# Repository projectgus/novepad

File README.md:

Development of an adapter board design for [Kosagi Novena](http://kosagi.com/w/index.php?title=Novena_Main_Page) LVDS interface to connect to the "iPad 3" QXGA 2048x1536 eDP LCD panel (aka LG LP097QX1-SPC1 and related models). Possibly also a touch screen interface to suit that display...

* [Schematic PDF here](https://github.com/projectgus/novepad/raw/master/novepad-schematic.pdf)
* [Kosagi forum thread here](http://www.kosagi.com/forums/viewtopic.php?id=58).

**INITIAL PROTOTYPE STAGE, NOT A THING YET**

Very closely modelled on Bunnie's existing Novena eDP adapter, with additions. LVDS connection cable from Novena should be the same on both boards.

Designed using KiCad (2014-07-25, any recent version should be OK to open the files). [Gerbers are available from the releases page](https://github.com/projectgus/novepad/releases/).

# Additions to the Novena eDP design

* Backlight driver (2x TI [TPS61181](http://www.ti.com/product/tps61181))
* Touch screen controller Focaltech [FT5816LPC](http://www.focaltech-systems.com/En/solutions.aspx?CateID=54) with i2c and USB interfaces. There's a strong chance this will never work (lack of public documentation on controller or digitizer).
* 4 eDP lanes out of IT6251 eDP converter instead of the 2 used on Novena eDP board.

# Notes

* Has a lot of numbered test points and 0R resistors due to undocumented or unknown factors.
* Has cut trace jumpers for some key power connections, can be cut to measure power consumption.

# Board Stackup

4 layer board, 1oz copper (35um). Desired stackup is:

* Front copper
* 0.2mm prepreg
* GND (Inner1)
* 1.2mm prepreg
* VCC (Inner2)
* 0.2mm prepreg
* Back

(This matches standard 4 layer stackup for my usual prototype PCB supplier, [Hackvana](http://hackvana.com)).)

The 100 ohm differential microstrip traces (LVDS, eDP) are routed as 0.2mm trace / 0.15mm spacing (~8/6 imperial), at least where possible. This yields estimates in the range of 99.5-102ohm differential impedance depending on who you ask (assuming Er 4.4, calculated using [TNT Field Solver](http://mmtl.sourceforge.net/) and [Jean Nicolle's impedance calculator](http://www.fedevel.com/welldoneblog/2011/08/pcb-impedance-calculator-single-ended-differential-pair/).

# Resources

## Novena designs

Yay OSHW!

* http://kosagi.com/w/index.php?title=Novena_PVT_Design_Source

## iPad display/connectors

* http://emerythacks.blogspot.com.au/2013/04/connecting-ipad-retina-lcd-to-pc.html
* http://mikesmods.com/mm-wp/?s=ipad+3

## Photos of IT6251

You know a chip is going to be fun when **photos** of PCBs that use it become a useful resource to complement the datasheet.

* [overclock.net post with high-res photo of top of board](http://www.overclock.net/t/1225919/yamakasi-catleap-monitor-club/2110#post_16887300)
* [overclock.net lower-res photos incl back of board (no components)](http://www.overclock.net/t/1304102/catleap-q270-replacement-board#post_18163044)

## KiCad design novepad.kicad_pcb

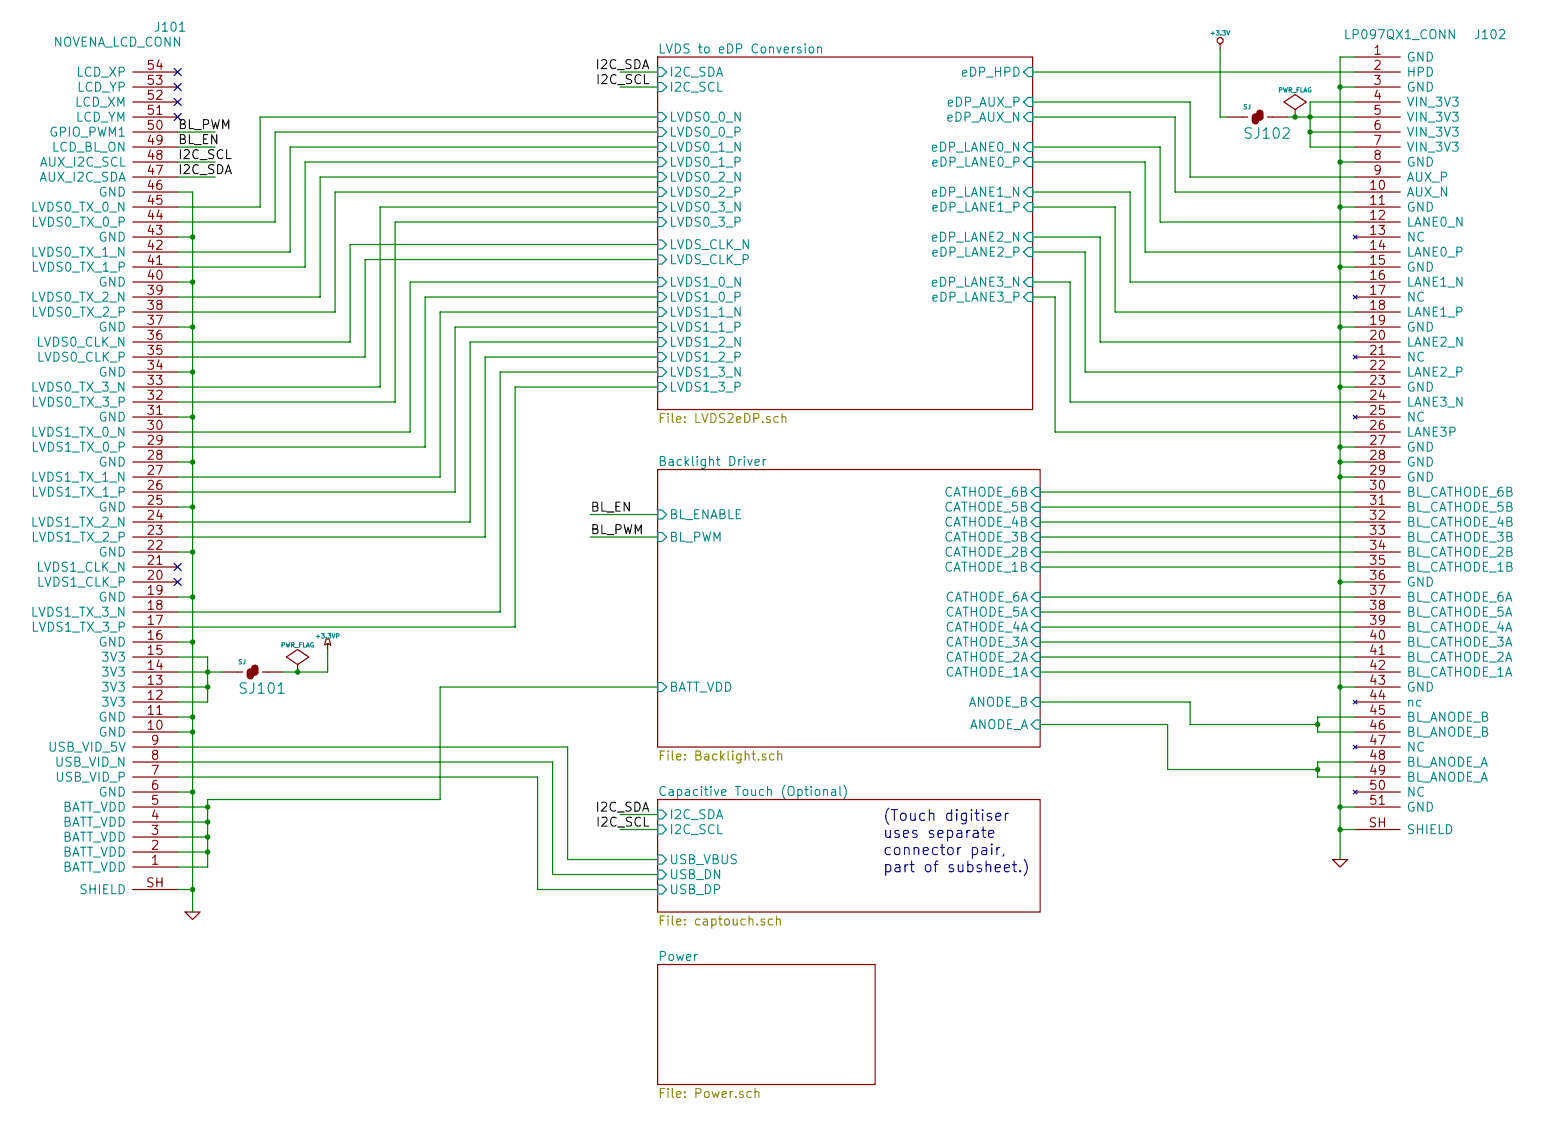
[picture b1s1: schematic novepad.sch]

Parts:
J101: NOVENA_LCD_CONN; MOLEX_51926_5494
J102: LP097QX1_CONN; MOLEX_502250_8051
SJ101, SJ102: SJ; SJ_SHORTED

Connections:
+3.3V: SJ102.1; also elsewhere on the board
+3.3VP: SJ101.2; also elsewhere on the board
/Backlight Driver/ANODE_A: J102.48 (BL_ANODE_A), J102.49 (BL_ANODE_A); also elsewhere on the board
/Backlight Driver/ANODE_B: J102.45 (BL_ANODE_B), J102.46 (BL_ANODE_B); also elsewhere on the board
/Backlight Driver/BATT_VDD: J101.1 (BATT_VDD), J101.2 (BATT_VDD), J101.3 (BATT_VDD), J101.4 (BATT_VDD), J101.5 (BATT_VDD); also elsewhere on the board
/Backlight Driver/BL_ENABLE: J101.49 (LCD_BL_ON); also elsewhere on the board
/Backlight Driver/BL_PWM: J101.50 (GPIO_PWM1); also elsewhere on the board
/Backlight Driver/CATHODE_1A: J102.42 (BL_CATHODE_1A); also elsewhere on the board
/Backlight Driver/CATHODE_1B: J102.35 (BL_CATHODE_1B); also elsewhere on the board
/Backlight Driver/CATHODE_2A: J102.41 (BL_CATHODE_2A); also elsewhere on the board
/Backlight Driver/CATHODE_2B: J102.34 (BL_CATHODE_2B); also elsewhere on the board
/Backlight Driver/CATHODE_3A: J102.40 (BL_CATHODE_3A); also elsewhere on the board
/Backlight Driver/CATHODE_3B: J102.33 (BL_CATHODE_3B); also elsewhere on the board
/Backlight Driver/CATHODE_4A: J102.39 (BL_CATHODE_4A); also elsewhere on the board
/Backlight Driver/CATHODE_4B: J102.32 (BL_CATHODE_4B); also elsewhere on the board
/Backlight Driver/CATHODE_5A: J102.38 (BL_CATHODE_5A); also elsewhere on the board
/Backlight Driver/CATHODE_5B: J102.31 (BL_CATHODE_5B); also elsewhere on the board
/Backlight Driver/CATHODE_6A: J102.37 (BL_CATHODE_6A); also elsewhere on the board
/Backlight Driver/CATHODE_6B: J102.30 (BL_CATHODE_6B); also elsewhere on the board
/Capacitive Touch (Optional)/I2C_SCL: J101.48 (AUX_I2C_SCL); also elsewhere on the board
/Capacitive Touch (Optional)/I2C_SDA: J101.47 (AUX_I2C_SDA); also elsewhere on the board
/Capacitive Touch (Optional)/USB_DN: J101.8 (USB_VID_N); also elsewhere on the board
/Capacitive Touch (Optional)/USB_DP: J101.7 (USB_VID_P); also elsewhere on the board
/Capacitive Touch (Optional)/USB_VBUS: J101.9 (USB_VID_5V); also elsewhere on the board
/LVDS to eDP Conversion/LVDS0_0_N: J101.45 (LVDS0_TX_0_N); also elsewhere on the board
/LVDS to eDP Conversion/LVDS0_0_P: J101.44 (LVDS0_TX_0_P); also elsewhere on the board
/LVDS to eDP Conversion/LVDS0_1_N: J101.42 (LVDS0_TX_1_N); also elsewhere on the board
/LVDS to eDP Conversion/LVDS0_1_P: J101.41 (LVDS0_TX_1_P); also elsewhere on the board
/LVDS to eDP Conversion/LVDS0_2_N: J101.39 (LVDS0_TX_2_N); also elsewhere on the board
/LVDS to eDP Conversion/LVDS0_2_P: J101.38 (LVDS0_TX_2_P); also elsewhere on the board
/LVDS to eDP Conversion/LVDS0_3_N: J101.33 (LVDS0_TX_3_N); also elsewhere on the board
/LVDS to eDP Conversion/LVDS0_3_P: J101.32 (LVDS0_TX_3_P); also elsewhere on the board
/LVDS to eDP Conversion/LVDS1_0_N: J101.30 (LVDS1_TX_0_N); also elsewhere on the board
/LVDS to eDP Conversion/LVDS1_0_P: J101.29 (LVDS1_TX_0_P); also elsewhere on the board
/LVDS to eDP Conversion/LVDS1_1_N: J101.27 (LVDS1_TX_1_N); also elsewhere on the board
/LVDS to eDP Conversion/LVDS1_1_P: J101.26 (LVDS1_TX_1_P); also elsewhere on the board
/LVDS to eDP Conversion/LVDS1_2_N: J101.24 (LVDS1_TX_2_N); also elsewhere on the board
/LVDS to eDP Conversion/LVDS1_2_P: J101.23 (LVDS1_TX_2_P); also elsewhere on the board
/LVDS to eDP Conversion/LVDS1_3_N: J101.18 (LVDS1_TX_3_N); also elsewhere on the board
/LVDS to eDP Conversion/LVDS1_3_P: J101.17 (LVDS1_TX_3_P); also elsewhere on the board
/LVDS to eDP Conversion/LVDS_CLK_N: J101.36 (LVDS0_CLK_N); also elsewhere on the board
/LVDS to eDP Conversion/LVDS_CLK_P: J101.35 (LVDS0_CLK_P); also elsewhere on the board
/LVDS to eDP Conversion/eDP_AUX_N: J102.10 (AUX_N); also elsewhere on the board
/LVDS to eDP Conversion/eDP_AUX_P: J102.9 (AUX_P); also elsewhere on the board
/LVDS to eDP Conversion/eDP_HPD: J102.2 (HPD); also elsewhere on the board
/LVDS to eDP Conversion/eDP_LANE0_N: J102.12 (LANE0_N); also elsewhere on the board
/LVDS to eDP Conversion/eDP_LANE0_P: J102.14 (LANE0_P); also elsewhere on the board
/LVDS to eDP Conversion/eDP_LANE1_N: J102.16 (LANE1_N); also elsewhere on the board
/LVDS to eDP Conversion/eDP_LANE1_P: J102.18 (LANE1_P); also elsewhere on the board
/LVDS to eDP Conversion/eDP_LANE2_N: J102.20 (LANE2_N); also elsewhere on the board
/LVDS to eDP Conversion/eDP_LANE2_P: J102.22 (LANE2_P); also elsewhere on the board
/LVDS to eDP Conversion/eDP_LANE3_N: J102.24 (LANE3_N); also elsewhere on the board
/LVDS to eDP Conversion/eDP_LANE3_P: J102.26 (LANE3P); also elsewhere on the board
GND: J101.6 (GND), J101.10 (GND), J101.11 (GND), J101.16 (GND), J101.19 (GND), J101.22 (GND), J101.25 (GND), J101.28 (GND), J101.31 (GND), J101.34 (GND), J101.37 (GND), J101.40 (GND), J101.43 (GND), J101.46 (GND), J101.SH (SHIELD), J102.1 (GND), J102.3 (GND), J102.8 (GND), J102.11 (GND), J102.15 (GND), J102.19 (GND), J102.23 (GND), J102.27 (GND), J102.28 (GND), J102.29 (GND), J102.36 (GND), J102.43 (GND), J102.51 (GND), J102.SH (SHIELD); also elsewhere on the board
unnamed: J101.12 (3V3), J101.13 (3V3), J101.14 (3V3), J101.15 (3V3), SJ101.1
unnamed: J102.4 (VIN_3V3), J102.5 (VIN_3V3), J102.6 (VIN_3V3), J102.7 (VIN_3V3), SJ102.2

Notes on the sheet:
(Touch digitiser uses separate connector pair, part of subsheet.)

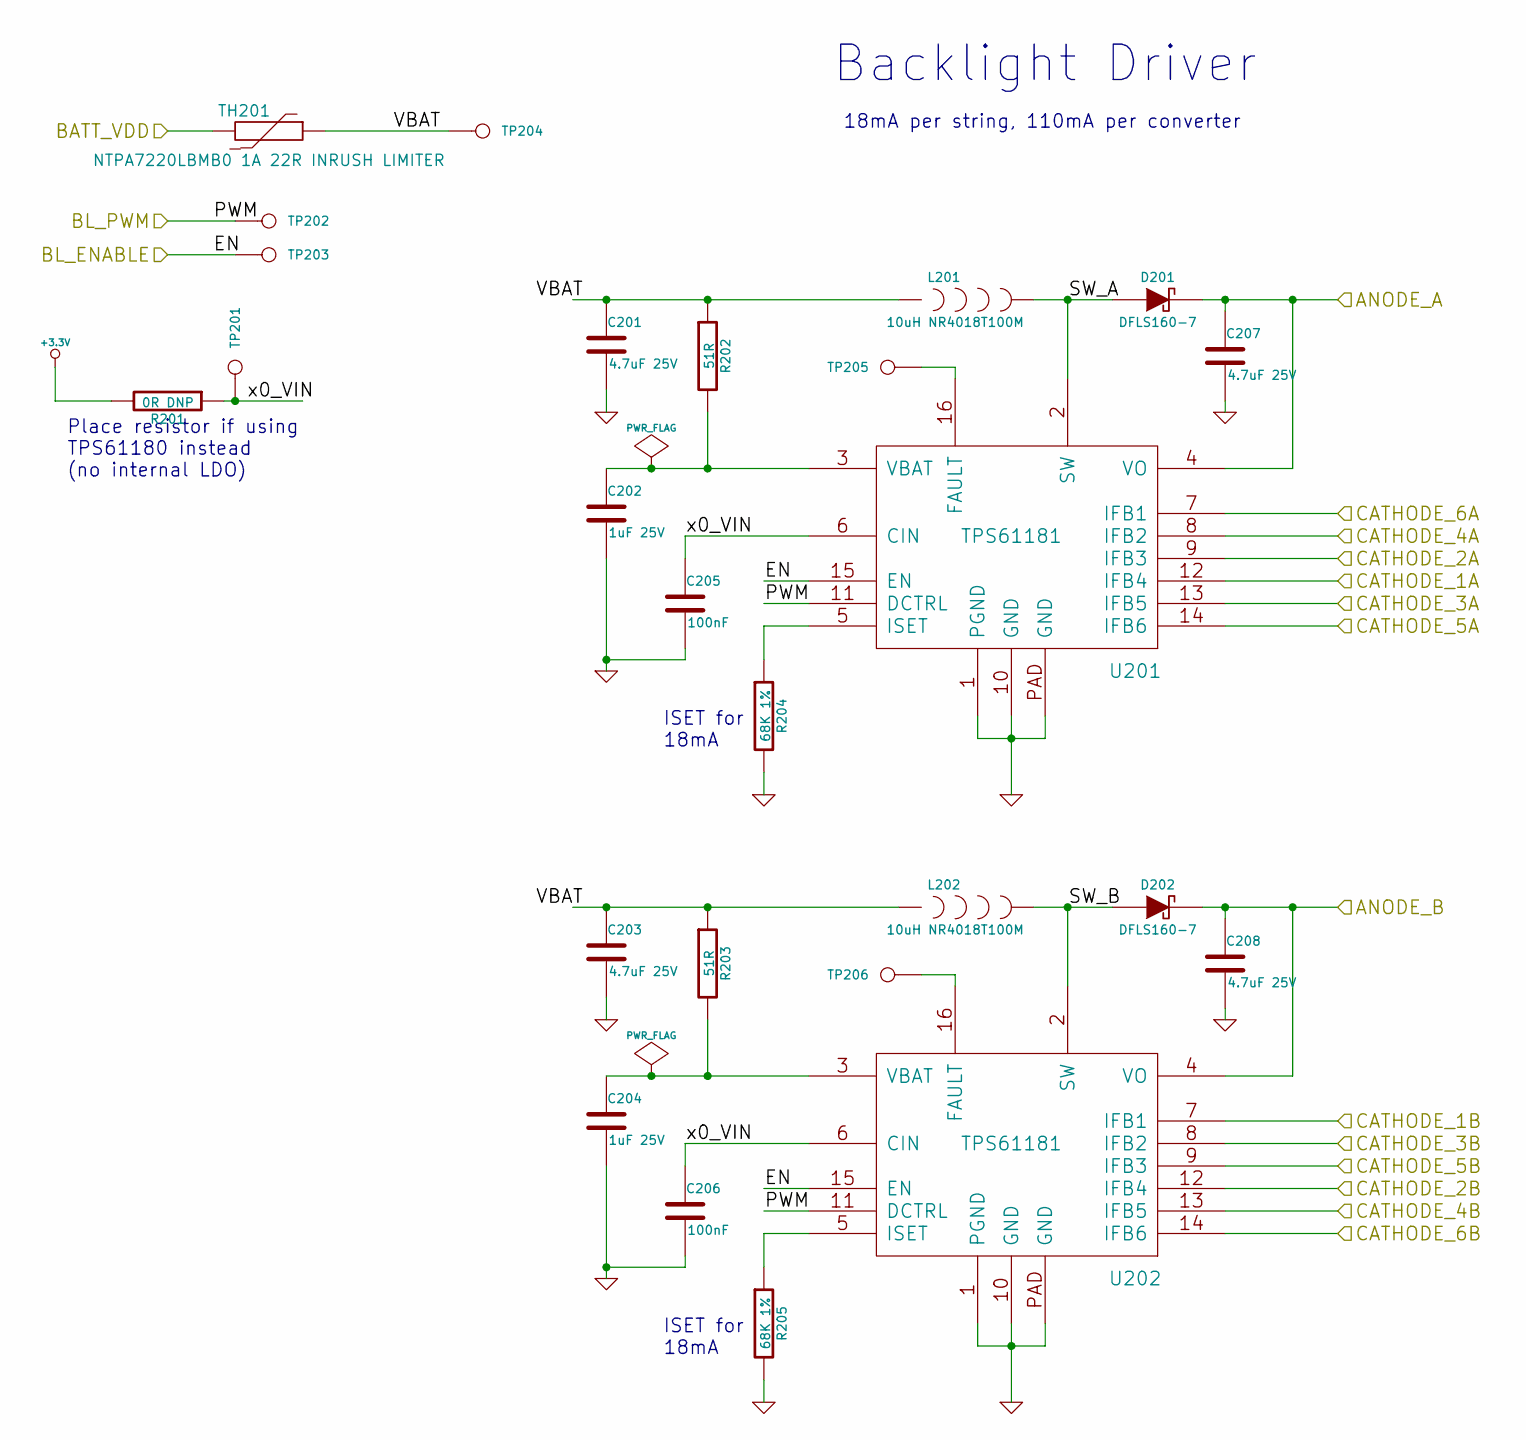
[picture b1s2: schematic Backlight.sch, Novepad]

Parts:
C201, C203, C207, C208: 4.7uF 25V; 0805
C202, C204: 1uF 25V; 0603
C205, C206: 100nF; C0402
D201, D202: DFLS160-7; POWERDI123_DIODE
L201, L202: 10uH NR4018T100M; NR4018_IND
R201: 0R DNP; 0603
R202, R203: 51R; 0603
R204, R205: 68K 1%; 0603
TH201: NTPA7220LBMB0 1A 22R INRUSH LIMITER; PTH_2HOLE_5MM
TP201, TP202, TP203, TP204, TP205, TP206: CONN_1; SMD_TEST_POINT
U201, U202: TPS61181; QFN50P300X300X80-17N

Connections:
+3.3V: R201.2; also elsewhere on the board
/Backlight Driver/ANODE_A: C207.1, D201.K, U201.4 (VO); also elsewhere on the board
/Backlight Driver/ANODE_B: C208.1, D202.K, U202.4 (VO); also elsewhere on the board
/Backlight Driver/BATT_VDD: TH201.2; also elsewhere on the board
/Backlight Driver/BL_ENABLE: TP203.1, U201.15 (EN), U202.15 (EN); also elsewhere on the board
/Backlight Driver/BL_PWM: TP202.1, U201.11 (DCTRL), U202.11 (DCTRL); also elsewhere on the board
/Backlight Driver/CATHODE_1A: U201.12 (IFB4); also elsewhere on the board
/Backlight Driver/CATHODE_1B: U202.7 (IFB1); also elsewhere on the board
/Backlight Driver/CATHODE_2A: U201.9 (IFB3); also elsewhere on the board
/Backlight Driver/CATHODE_2B: U202.12 (IFB4); also elsewhere on the board
/Backlight Driver/CATHODE_3A: U201.13 (IFB5); also elsewhere on the board
/Backlight Driver/CATHODE_3B: U202.8 (IFB2); also elsewhere on the board
/Backlight Driver/CATHODE_4A: U201.8 (IFB2); also elsewhere on the board
/Backlight Driver/CATHODE_4B: U202.13 (IFB5); also elsewhere on the board
/Backlight Driver/CATHODE_5A: U201.14 (IFB6); also elsewhere on the board
/Backlight Driver/CATHODE_5B: U202.9 (IFB3); also elsewhere on the board
/Backlight Driver/CATHODE_6A: U201.7 (IFB1); also elsewhere on the board
/Backlight Driver/CATHODE_6B: U202.14 (IFB6); also elsewhere on the board
/Backlight Driver/SW_A: D201.A, L201.2, U201.2 (SW)
/Backlight Driver/SW_B: D202.A, L202.2, U202.2 (SW)
/Backlight Driver/VBAT: C201.1, C203.1, L201.1, L202.1, R202.1, R203.1, TH201.1, TP204.1
/Backlight Driver/x0_VIN: C205.1, C206.1, R201.1, TP201.1, U201.6 (CIN), U202.6 (CIN)
GND: C201.2, C202.2, C203.2, C204.2, C205.2, C206.2, C207.2, C208.2, R204.2, R205.2, U201.1 (PGND), U201.10 (GND), U201.PAD (GND), U202.1 (PGND), U202.10 (GND), U202.PAD (GND); also elsewhere on the board
unnamed: C202.1, R202.2, U201.3 (VBAT)
unnamed: C204.1, R203.2, U202.3 (VBAT)
unnamed: R204.1, U201.5 (ISET)
unnamed: R205.1, U202.5 (ISET)
unnamed: TP205.1, U201.16 (FAULT)
unnamed: TP206.1, U202.16 (FAULT)

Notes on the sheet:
Place resistor if using TPS61180 instead (no internal LDO)
18mA per string, 110mA per converter
ISET for 18mA
Backlight Driver

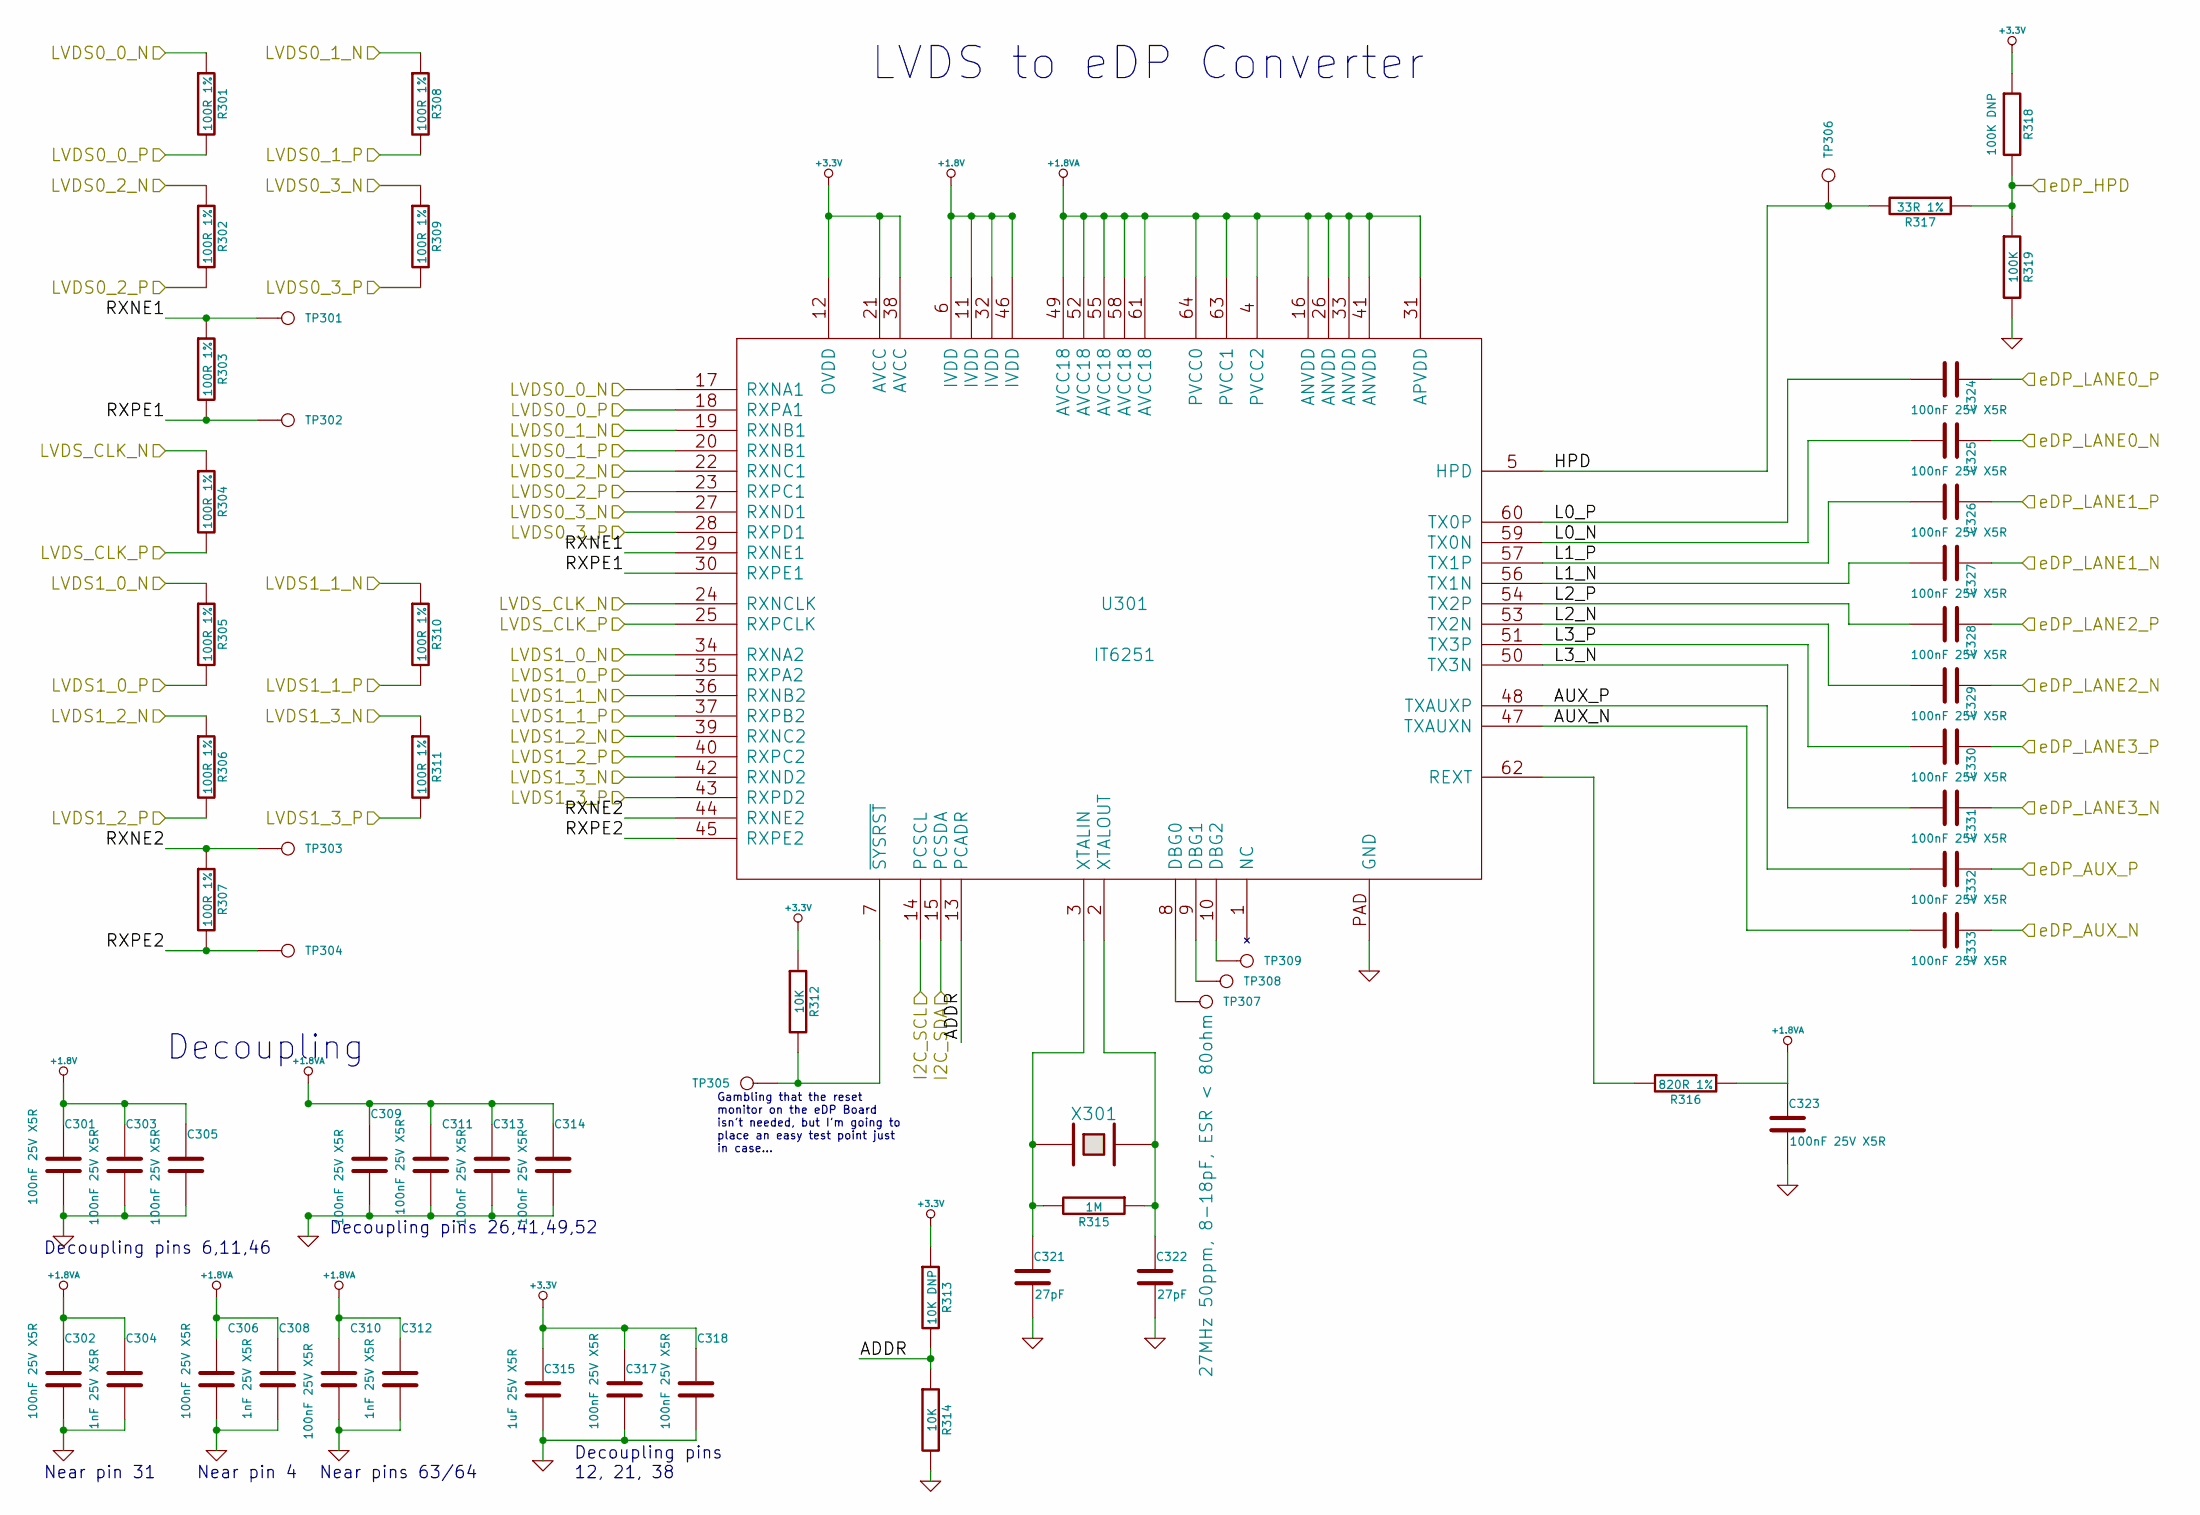
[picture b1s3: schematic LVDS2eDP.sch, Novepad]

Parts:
C301, C302, C303, C305, C306, C309, C310, C311, C313, C314, C317, C318, C323, C324, C325, C326, C327, C328, C329, C330, C331, C332, C333: 100nF 25V X5R; SMD-0402_c
C304, C308, C312: 1nF 25V X5R; SMD-0402_c
C315: 1uF 25V X5R; SMD-0402_c
C321, C322: 27pF; 0603
R301, R302, R303, R304, R305, R306, R307, R308, R309, R310, R311: 100R 1%; SMD-0402_r
R312, R314: 10K; 0603
R313: 10K DNP; 0603
R315: 1M; 0603
R316: 820R 1%; 0603
R317: 33R 1%; 0603
R318: 100K DNP; 0603
R319: 100K; 0603
TP301, TP302, TP303, TP304, TP305, TP306, TP307, TP308, TP309: CONN_1; SMD_TEST_POINT
U301: IT6251; QFN50P900X900X100-65N
X301: 27MHz 50ppm, 8-18pF, ESR < 80ohm; HC49UP

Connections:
+1.8V: C301.1, C303.1, C305.1, U301.6 (IVDD), U301.11 (IVDD), U301.32 (IVDD), U301.46 (IVDD); also elsewhere on the board
+1.8VA: C302.1, C304.1, C306.1, C308.1, C309.1, C310.1, C311.1, C312.1, C313.1, C314.1, C323.1, R316.1, U301.4 (PVCC2), U301.16 (ANVDD), U301.26 (ANVDD), U301.31 (APVDD), U301.33 (ANVDD), U301.41 (ANVDD), U301.49 (AVCC18), U301.52 (AVCC18), U301.55 (AVCC18), U301.58 (AVCC18), U301.61 (AVCC18), U301.63 (PVCC1), U301.64 (PVCC0); also elsewhere on the board
+3.3V: C315.1, C317.1, C318.1, R312.1, R313.1, R318.1, U301.12 (OVDD), U301.21 (AVCC), U301.38 (AVCC); also elsewhere on the board
/Capacitive Touch (Optional)/I2C_SCL: U301.14 (PCSCL); also elsewhere on the board
/Capacitive Touch (Optional)/I2C_SDA: U301.15 (PCSDA); also elsewhere on the board
/LVDS to eDP Conversion/ADDR: R313.2, R314.1, U301.13 (PCADR)
/LVDS to eDP Conversion/AUX_N: C333.2, U301.47 (TXAUXN)
/LVDS to eDP Conversion/AUX_P: C332.2, U301.48 (TXAUXP)
/LVDS to eDP Conversion/HPD: R317.2, TP306.1, U301.5 (HPD)
/LVDS to eDP Conversion/L0_N: C325.2, U301.59 (TX0N)
/LVDS to eDP Conversion/L0_P: C324.2, U301.60 (TX0P)
/LVDS to eDP Conversion/L1_N: C327.2, U301.56 (TX1N)
/LVDS to eDP Conversion/L1_P: C326.2, U301.57 (TX1P)
/LVDS to eDP Conversion/L2_N: C329.2, U301.53 (TX2N)
/LVDS to eDP Conversion/L2_P: C328.2, U301.54 (TX2P)
/LVDS to eDP Conversion/L3_N: C331.2, U301.50 (TX3N)
/LVDS to eDP Conversion/L3_P: C330.2, U301.51 (TX3P)
/LVDS to eDP Conversion/LVDS0_0_N: R301.1, U301.17 (RXNA1); also elsewhere on the board
/LVDS to eDP Conversion/LVDS0_0_P: R301.2, U301.18 (RXPA1); also elsewhere on the board
/LVDS to eDP Conversion/LVDS0_1_N: R308.1, U301.19 (RXNB1); also elsewhere on the board
/LVDS to eDP Conversion/LVDS0_1_P: R308.2, U301.20 (RXNB1); also elsewhere on the board
/LVDS to eDP Conversion/LVDS0_2_N: R302.1, U301.22 (RXNC1); also elsewhere on the board
/LVDS to eDP Conversion/LVDS0_2_P: R302.2, U301.23 (RXPC1); also elsewhere on the board
/LVDS to eDP Conversion/LVDS0_3_N: R309.1, U301.27 (RXND1); also elsewhere on the board
/LVDS to eDP Conversion/LVDS0_3_P: R309.2, U301.28 (RXPD1); also elsewhere on the board
/LVDS to eDP Conversion/LVDS1_0_N: R305.1, U301.34 (RXNA2); also elsewhere on the board
/LVDS to eDP Conversion/LVDS1_0_P: R305.2, U301.35 (RXPA2); also elsewhere on the board
/LVDS to eDP Conversion/LVDS1_1_N: R310.1, U301.36 (RXNB2); also elsewhere on the board
/LVDS to eDP Conversion/LVDS1_1_P: R310.2, U301.37 (RXPB2); also elsewhere on the board
/LVDS to eDP Conversion/LVDS1_2_N: R306.1, U301.39 (RXNC2); also elsewhere on the board
/LVDS to eDP Conversion/LVDS1_2_P: R306.2, U301.40 (RXPC2); also elsewhere on the board
/LVDS to eDP Conversion/LVDS1_3_N: R311.1, U301.42 (RXND2); also elsewhere on the board
/LVDS to eDP Conversion/LVDS1_3_P: R311.2, U301.43 (RXPD2); also elsewhere on the board
/LVDS to eDP Conversion/LVDS_CLK_N: R304.1, U301.24 (RXNCLK); also elsewhere on the board
/LVDS to eDP Conversion/LVDS_CLK_P: R304.2, U301.25 (RXPCLK); also elsewhere on the board
/LVDS to eDP Conversion/RXNE1: R303.1, TP301.1, U301.29 (RXNE1)
/LVDS to eDP Conversion/RXNE2: R307.1, TP303.1, U301.44 (RXNE2)
/LVDS to eDP Conversion/RXPE1: R303.2, TP302.1, U301.30 (RXPE1)
/LVDS to eDP Conversion/RXPE2: R307.2, TP304.1, U301.45 (RXPE2)
/LVDS to eDP Conversion/eDP_AUX_N: C333.1; also elsewhere on the board
/LVDS to eDP Conversion/eDP_AUX_P: C332.1; also elsewhere on the board
/LVDS to eDP Conversion/eDP_HPD: R317.1, R318.2, R319.1; also elsewhere on the board
/LVDS to eDP Conversion/eDP_LANE0_N: C325.1; also elsewhere on the board
/LVDS to eDP Conversion/eDP_LANE0_P: C324.1; also elsewhere on the board
/LVDS to eDP Conversion/eDP_LANE1_N: C327.1; also elsewhere on the board
/LVDS to eDP Conversion/eDP_LANE1_P: C326.1; also elsewhere on the board
/LVDS to eDP Conversion/eDP_LANE2_N: C329.1; also elsewhere on the board
/LVDS to eDP Conversion/eDP_LANE2_P: C328.1; also elsewhere on the board
/LVDS to eDP Conversion/eDP_LANE3_N: C331.1; also elsewhere on the board
/LVDS to eDP Conversion/eDP_LANE3_P: C330.1; also elsewhere on the board
GND: C301.2, C302.2, C303.2, C304.2, C305.2, C306.2, C308.2, C309.2, C310.2, C311.2, C312.2, C313.2, C314.2, C315.2, C317.2, C318.2, C321.2, C322.2, C323.2, R314.2, R319.2, U301.PAD (GND); also elsewhere on the board
unnamed: C321.1, R315.2, U301.3 (XTALIN), X301.1
unnamed: C322.1, R315.1, U301.2 (XTALOUT), X301.2
unnamed: R312.2, TP305.1, U301.7 (~SYSRST)
unnamed: R316.2, U301.62 (REXT)
unnamed: TP307.1, U301.8 (DBG0)
unnamed: TP308.1, U301.9 (DBG1)
unnamed: TP309.1, U301.10 (DBG2)

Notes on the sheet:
Gambling that the reset monitor on the eDP Board isn't needed, but I'm going to place an easy test point just in case...
Decoupling pins 12, 21, 38
Decoupling pins 26,41,49,52
Near pin 31
Near pin 4
Decoupling
Near pins 63/64
LVDS to eDP Converter
Decoupling pins 6,11,46

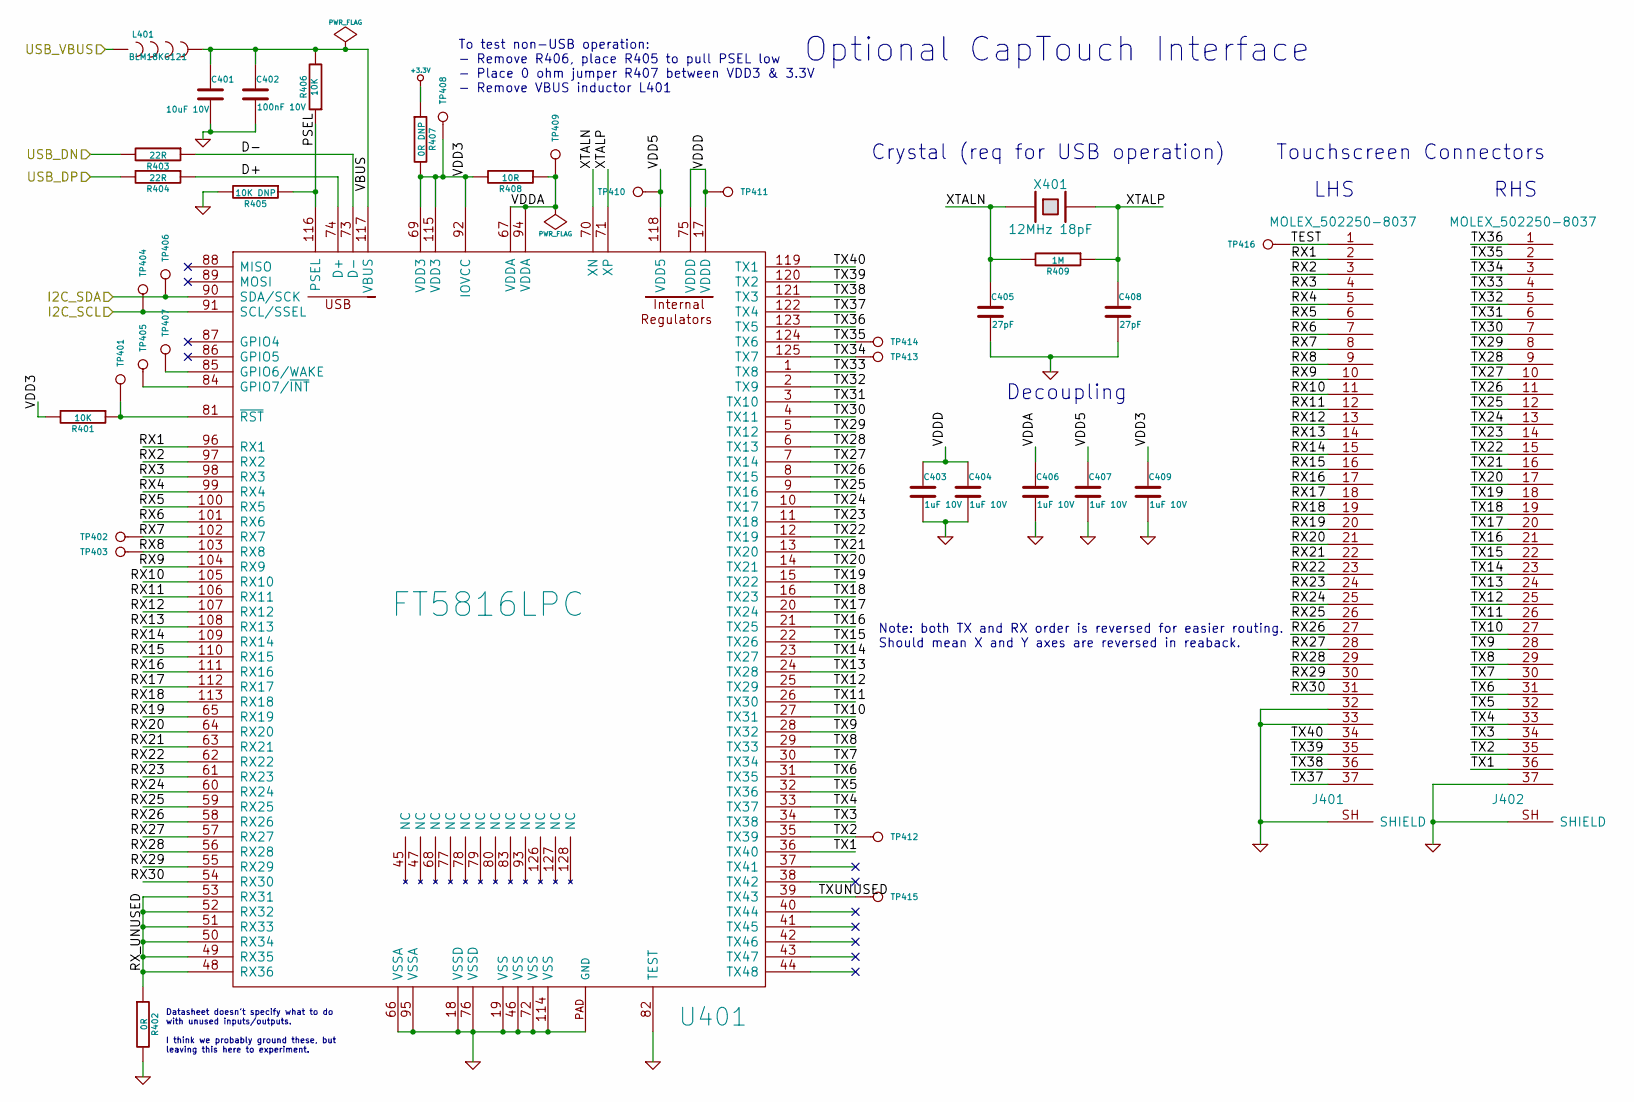
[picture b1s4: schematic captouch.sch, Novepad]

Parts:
C401: 10uF 10V; 1206
C402: 100nF 10V; C0402
C403, C404, C406, C407, C409: 1uF 10V; 0603
C405, C408: 27pF; 0603
J401, J402: MOLEX_502250-8037; MOLEX_502250_8037
L401: BLM18KG121; 0603
R401, R406: 10K; 0603
R402: 0R; 0603
R403, R404: 22R; 0603
R405: 10K DNP; 0603
R407: 0R DNP; 0603
R408: 10R; 0603
R409: 1M; 0603
TP401, TP402, TP403, TP404, TP405, TP406, TP407, TP408, TP409, TP410, TP411, TP412, TP413, TP414, TP415, TP416: CONN_1; SMD_TEST_POINT
U401: FT5816LPC; QFP40P1600X1600X100-129N
X401: 12MHz 18pF; HC49UP

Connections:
+3.3V: R407.1; also elsewhere on the board
/Capacitive Touch (Optional)/D+: R404.1, U401.74 (D+)
/Capacitive Touch (Optional)/D-: R403.1, U401.73 (D-)
/Capacitive Touch (Optional)/I2C_SCL: TP404.1, U401.91 (SCL/SSEL); also elsewhere on the board
/Capacitive Touch (Optional)/I2C_SDA: TP406.1, U401.90 (SDA/SCK); also elsewhere on the board
/Capacitive Touch (Optional)/PSEL: R405.1, R406.1, U401.116 (PSEL)
/Capacitive Touch (Optional)/RX1: J401.2, U401.96 (RX1)
/Capacitive Touch (Optional)/RX2: J401.3, U401.97 (RX2)
/Capacitive Touch (Optional)/RX3: J401.4, U401.98 (RX3)
/Capacitive Touch (Optional)/RX4: J401.5, U401.99 (RX4)
/Capacitive Touch (Optional)/RX5: J401.6, U401.100 (RX5)
/Capacitive Touch (Optional)/RX6: J401.7, U401.101 (RX6)
/Capacitive Touch (Optional)/RX7: J401.8, TP402.1, U401.102 (RX7)
/Capacitive Touch (Optional)/RX8: J401.9, TP403.1, U401.103 (RX8)
/Capacitive Touch (Optional)/RX9: J401.10, U401.104 (RX9)
/Capacitive Touch (Optional)/RX10: J401.11, U401.105 (RX10)
/Capacitive Touch (Optional)/RX11: J401.12, U401.106 (RX11)
/Capacitive Touch (Optional)/RX12: J401.13, U401.107 (RX12)
/Capacitive Touch (Optional)/RX13: J401.14, U401.108 (RX13)
/Capacitive Touch (Optional)/RX14: J401.15, U401.109 (RX14)
/Capacitive Touch (Optional)/RX15: J401.16, U401.110 (RX15)
/Capacitive Touch (Optional)/RX16: J401.17, U401.111 (RX16)
/Capacitive Touch (Optional)/RX17: J401.18, U401.112 (RX17)
/Capacitive Touch (Optional)/RX18: J401.19, U401.113 (RX18)
/Capacitive Touch (Optional)/RX19: J401.20, U401.65 (RX19)
/Capacitive Touch (Optional)/RX20: J401.21, U401.64 (RX20)
/Capacitive Touch (Optional)/RX21: J401.22, U401.63 (RX21)
/Capacitive Touch (Optional)/RX22: J401.23, U401.62 (RX22)
/Capacitive Touch (Optional)/RX23: J401.24, U401.61 (RX23)
/Capacitive Touch (Optional)/RX24: J401.25, U401.60 (RX24)
/Capacitive Touch (Optional)/RX25: J401.26, U401.59 (RX25)
/Capacitive Touch (Optional)/RX26: J401.27, U401.58 (RX26)
/Capacitive Touch (Optional)/RX27: J401.28, U401.57 (RX27)
/Capacitive Touch (Optional)/RX28: J401.29, U401.56 (RX28)
/Capacitive Touch (Optional)/RX29: J401.30, U401.55 (RX29)
/Capacitive Touch (Optional)/RX30: J401.31, U401.54 (RX30)
/Capacitive Touch (Optional)/RX_UNUSED: R402.1, U401.48 (RX36), U401.49 (RX35), U401.50 (RX34), U401.51 (RX33), U401.52 (RX32), U401.53 (RX31)
/Capacitive Touch (Optional)/TEST: J401.1, TP416.1
/Capacitive Touch (Optional)/TX1: J402.36, U401.36 (TX40)
/Capacitive Touch (Optional)/TX2: J402.35, TP412.1, U401.35 (TX39)
/Capacitive Touch (Optional)/TX3: J402.34, U401.34 (TX38)
/Capacitive Touch (Optional)/TX4: J402.33, U401.33 (TX37)
/Capacitive Touch (Optional)/TX5: J402.32, U401.32 (TX36)
/Capacitive Touch (Optional)/TX6: J402.31, U401.31 (TX35)
/Capacitive Touch (Optional)/TX7: J402.30, U401.30 (TX34)
/Capacitive Touch (Optional)/TX8: J402.29, U401.29 (TX33)
/Capacitive Touch (Optional)/TX9: J402.28, U401.28 (TX32)
/Capacitive Touch (Optional)/TX10: J402.27, U401.27 (TX31)
/Capacitive Touch (Optional)/TX11: J402.26, U401.26 (TX30)
/Capacitive Touch (Optional)/TX12: J402.25, U401.25 (TX29)
/Capacitive Touch (Optional)/TX13: J402.24, U401.24 (TX28)
/Capacitive Touch (Optional)/TX14: J402.23, U401.23 (TX27)
/Capacitive Touch (Optional)/TX15: J402.22, U401.22 (TX26)
/Capacitive Touch (Optional)/TX16: J402.21, U401.21 (TX25)
/Capacitive Touch (Optional)/TX17: J402.20, U401.20 (TX24)
/Capacitive Touch (Optional)/TX18: J402.19, U401.16 (TX23)
/Capacitive Touch (Optional)/TX19: J402.18, U401.15 (TX22)
/Capacitive Touch (Optional)/TX20: J402.17, U401.14 (TX21)
/Capacitive Touch (Optional)/TX21: J402.16, U401.13 (TX20)
/Capacitive Touch (Optional)/TX22: J402.15, U401.12 (TX19)
/Capacitive Touch (Optional)/TX23: J402.14, U401.11 (TX18)
/Capacitive Touch (Optional)/TX24: J402.13, U401.10 (TX17)
/Capacitive Touch (Optional)/TX25: J402.12, U401.9 (TX16)
/Capacitive Touch (Optional)/TX26: J402.11, U401.8 (TX15)
/Capacitive Touch (Optional)/TX27: J402.10, U401.7 (TX14)
/Capacitive Touch (Optional)/TX28: J402.9, U401.6 (TX13)
/Capacitive Touch (Optional)/TX29: J402.8, U401.5 (TX12)
/Capacitive Touch (Optional)/TX30: J402.7, U401.4 (TX11)
/Capacitive Touch (Optional)/TX31: J402.6, U401.3 (TX10)
/Capacitive Touch (Optional)/TX32: J402.5, U401.2 (TX9)
/Capacitive Touch (Optional)/TX33: J402.4, U401.1 (TX8)
/Capacitive Touch (Optional)/TX34: J402.3, TP413.1, U401.125 (TX7)
/Capacitive Touch (Optional)/TX35: J402.2, TP414.1, U401.124 (TX6)
/Capacitive Touch (Optional)/TX36: J402.1, U401.123 (TX5)
/Capacitive Touch (Optional)/TX37: J401.37, U401.122 (TX4)
/Capacitive Touch (Optional)/TX38: J401.36, U401.121 (TX3)
/Capacitive Touch (Optional)/TX39: J401.35, U401.120 (TX2)
/Capacitive Touch (Optional)/TX40: J401.34, U401.119 (TX1)
/Capacitive Touch (Optional)/TXUNUSED: TP415.1, U401.39 (TX43)
/Capacitive Touch (Optional)/USB_DN: R403.2; also elsewhere on the board
/Capacitive Touch (Optional)/USB_DP: R404.2; also elsewhere on the board
/Capacitive Touch (Optional)/USB_VBUS: L401.1; also elsewhere on the board
/Capacitive Touch (Optional)/VBUS: C401.1, C402.1, L401.2, R406.2, U401.117 (VBUS)
/Capacitive Touch (Optional)/VDD3: C409.1, R401.2, R407.2, R408.2, TP408.1, U401.69 (VDD3), U401.92 (IOVCC), U401.115 (VDD3)
/Capacitive Touch (Optional)/VDD5: C407.1, TP410.1, U401.118 (VDD5)
/Capacitive Touch (Optional)/VDDA: C406.1, R408.1, TP409.1, U401.67 (VDDA), U401.94 (VDDA)
/Capacitive Touch (Optional)/VDDD: C403.1, C404.1, TP411.1, U401.17 (VDDD), U401.75 (VDDD)
/Capacitive Touch (Optional)/XTALN: C405.1, R409.2, U401.70 (XN), X401.1
/Capacitive Touch (Optional)/XTALP: C408.1, R409.1, U401.71 (XP), X401.2
GND: C401.2, C402.2, C403.2, C404.2, C405.2, C406.2, C407.2, C408.2, C409.2, J401.32, J401.33, J401.SH (SHIELD), J402.37, J402.SH (SHIELD), R402.2, R405.2, U401.18 (VSSD), U401.19 (VSS), U401.46 (VSS), U401.66 (VSSA), U401.72 (VSS), U401.76 (VSSD), U401.82 (TEST), U401.95 (VSSA), U401.114 (VSS), U401.PAD (GND); also elsewhere on the board
unnamed: R401.1, TP401.1, U401.81 (~RST)
unnamed: TP405.1, U401.84 (GPIO7/~INT)
unnamed: TP407.1, U401.85 (GPIO6/WAKE)

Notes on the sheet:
Crystal (req for USB operation)
Decoupling
Touchscreen Connectors
LHS
RHS
To test non-USB operation: - Remove R406, place R405 to pull PSEL low - Place 0 ohm jumper R407 between VDD3 & 3.3V - Remove VBUS inductor L401
Datasheet doesn't specify what to do with unused inputs/outputs. I think we probably ground these, but leaving this here to experiment.
Optional CapTouch Interface
Note: both TX and RX order is reversed for easier routing. Should mean X and Y axes are reversed in reaback.

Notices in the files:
Backlight.sch:
Creative Commons Attribution Sharealike License
novepad.kicad_pcb:
Apache 2.0 License
novepad.sch:
Creative Commons Attribution Sharealike License 3.0
